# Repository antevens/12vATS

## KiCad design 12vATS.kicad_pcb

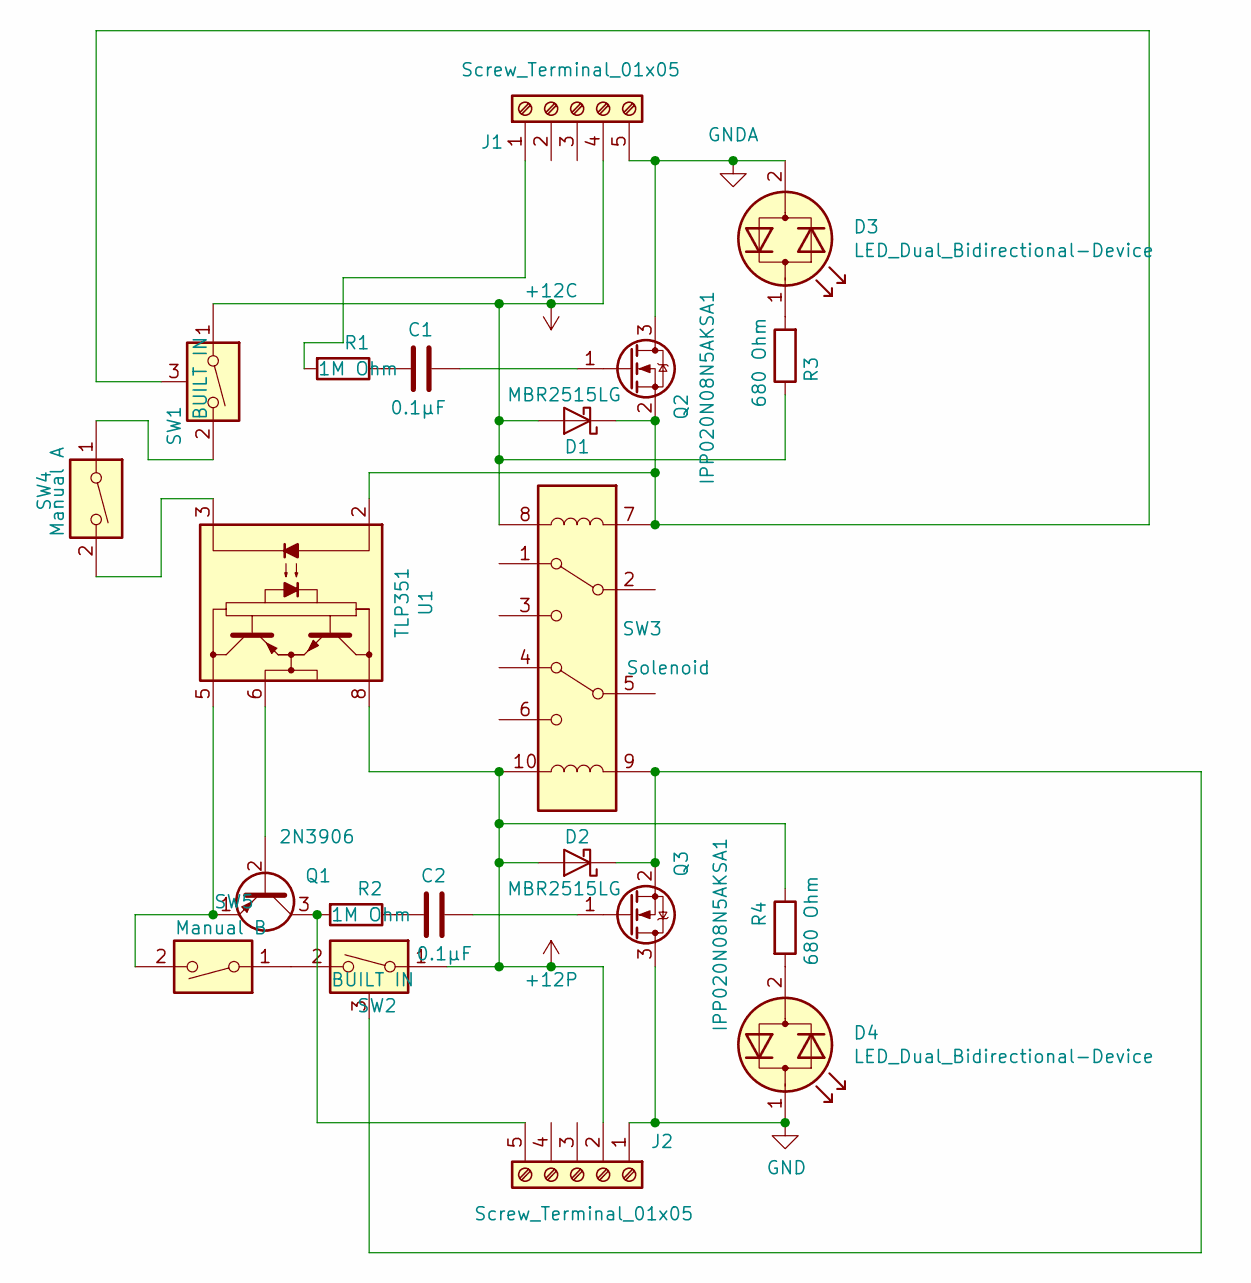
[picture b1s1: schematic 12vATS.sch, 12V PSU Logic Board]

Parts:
C1, C2: 0.1μF; C_Disc_D3.4mm_W2.1mm_P2.50mm
D1, D2: MBR2515LG; TO-220-2_Vertical
D3, D4: LED_Dual_Bidirectional-Device; LED_D5.0mm
J1, J2: Screw_Terminal_01x05; SolderWirePad_1x05_P3.81mm_Drill1.2mm
Q1: 2N3906; TO-92_Inline
Q2, Q3: IPP020N08N5AKSA1; TO-220-3_Vertical
R1, R2: 1M Ohm; R_Axial_DIN0207_L6.3mm_D2.5mm_P7.62mm_Horizontal
R3, R4: 680 Ohm; R_Axial_DIN0207_L6.3mm_D2.5mm_P7.62mm_Horizontal
SW1, SW2: BUILT IN; FanPinHeader_1x03_P2.54mm_Vertical
SW3: Solenoid
SW4: Manual A; SolderWirePad_1x02_P3.81mm_Drill1mm
SW5: Manual B; SolderWirePad_1x02_P3.81mm_Drill1mm
U1: TLP351; DIP-8_W7.62mm

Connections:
+12C: D1.2 (A), J1.4, R3.1, SW1.1, SW3.8
+12P: D2.2 (A), J2.2, R4.1, SW2.1, SW3.10, U1.8 (VCC)
GND: D4.1 (KA), J2.1, Q3.3 (D)
GNDA: D3.2 (AK), J1.5, Q2.3 (D)
unnamed: C1.1, R1.1
unnamed: C1.2, Q2.1 (G)
unnamed: C2.1, R2.1
unnamed: C2.2, Q3.1 (G)
unnamed: D1.1 (K), Q2.2 (S), SW1.3 (Pseudo), SW3.7, U1.2 (A)
unnamed: D2.1 (K), Q3.2 (S), SW2.3 (Pseudo), SW3.9
unnamed: D3.1 (KA), R3.2
unnamed: D4.2 (AK), R4.2
unnamed: J1.1, R1.2
unnamed: J2.5, Q1.3 (C), R2.2
unnamed: Q1.1 (E), SW5.2, U1.5 (VEE)
unnamed: Q1.2 (B), U1.6 (VO)
unnamed: SW1.2, SW4.1
unnamed: SW2.2, SW5.1
unnamed: SW4.2, U1.3 (C)

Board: 2 copper layers, 20 parts (0 on the bottom side), 19 nets, no tracks yet.
